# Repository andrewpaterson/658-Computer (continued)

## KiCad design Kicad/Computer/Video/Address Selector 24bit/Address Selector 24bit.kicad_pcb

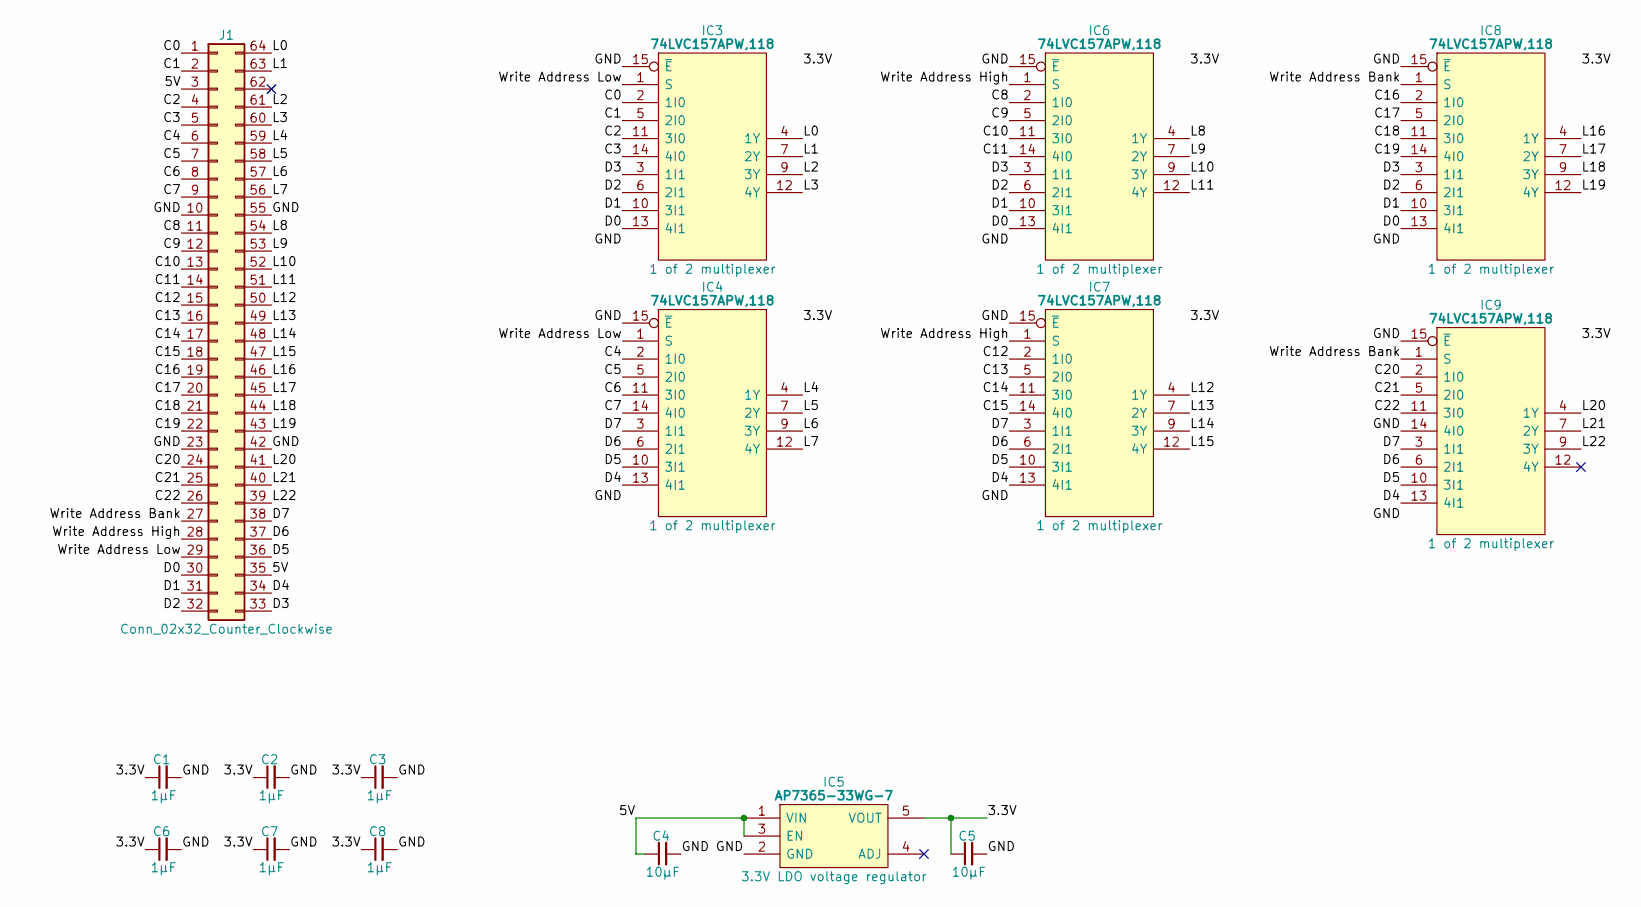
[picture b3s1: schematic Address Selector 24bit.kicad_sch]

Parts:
C1, C2, C3, C6, C7, C8: 1μF; C_0805
C4, C5: 10µF; C_0805
IC3, IC4, IC6, IC7, IC8, IC9: 74LVC157APW,118; SOP65P640X110-16N; Mouser Part Number 771-74LVC157APW-T
IC5: AP7365-33WG-7; SOT95P285X130-5N; Manufacturer_Part_Number AP7365-33WG-7; Mouser Part Number 621-AP7365-33WG-7
J1: Conn_02x32_Counter_Clockwise; DIP-64_Board_W15.24mm

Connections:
/3.3V: C1.1, C2.1, C3.1, C5.1, C6.1, C7.1, C8.1, IC3.16 (3V), IC4.16 (3V), IC5.5 (VOUT), IC6.16 (3V), IC7.16 (3V), IC8.16 (3V), IC9.16 (3V)
/5V: C4.1, IC5.1 (VIN), IC5.3 (EN), J1.3, J1.35
/C0: IC3.2 (1I0), J1.1
/C1: IC3.5 (2I0), J1.2
/C2: IC3.11 (3I0), J1.4
/C3: IC3.14 (4I0), J1.5
/C4: IC4.2 (1I0), J1.6
/C5: IC4.5 (2I0), J1.7
/C6: IC4.11 (3I0), J1.8
/C7: IC4.14 (4I0), J1.9
/C8: IC6.2 (1I0), J1.11
/C9: IC6.5 (2I0), J1.12
/C10: IC6.11 (3I0), J1.13
/C11: IC6.14 (4I0), J1.14
/C12: IC7.2 (1I0), J1.15
/C13: IC7.5 (2I0), J1.16
/C14: IC7.11 (3I0), J1.17
/C15: IC7.14 (4I0), J1.18
/C16: IC8.2 (1I0), J1.19
/C17: IC8.5 (2I0), J1.20
/C18: IC8.11 (3I0), J1.21
/C19: IC8.14 (4I0), J1.22
/C20: IC9.2 (1I0), J1.24
/C21: IC9.5 (2I0), J1.25
/C22: IC9.11 (3I0), J1.26
/D0: IC3.13 (4I1), IC6.13 (4I1), IC8.13 (4I1), J1.30
/D1: IC3.10 (3I1), IC6.10 (3I1), IC8.10 (3I1), J1.31
/D2: IC3.6 (2I1), IC6.6 (2I1), IC8.6 (2I1), J1.32
/D3: IC3.3 (1I1), IC6.3 (1I1), IC8.3 (1I1), J1.33
/D4: IC4.13 (4I1), IC7.13 (4I1), IC9.13 (4I1), J1.34
/D5: IC4.10 (3I1), IC7.10 (3I1), IC9.10 (3I1), J1.36
/D6: IC4.6 (2I1), IC7.6 (2I1), IC9.6 (2I1), J1.37
/D7: IC4.3 (1I1), IC7.3 (1I1), IC9.3 (1I1), J1.38
/GND: C1.2, C2.2, C3.2, C4.2, C5.2, C6.2, C7.2, C8.2, IC3.8 (GND), IC3.15 (~E), IC4.8 (GND), IC4.15 (~E), IC5.2 (GND), IC6.8 (GND), IC6.15 (~E), IC7.8 (GND), IC7.15 (~E), IC8.8 (GND), IC8.15 (~E), IC9.8 (GND), IC9.14 (4I0), IC9.15 (~E), J1.10, J1.23, J1.42, J1.55
/L0: IC3.4 (1Y), J1.64
/L1: IC3.7 (2Y), J1.63
/L2: IC3.9 (3Y), J1.61
/L3: IC3.12 (4Y), J1.60
/L4: IC4.4 (1Y), J1.59
/L5: IC4.7 (2Y), J1.58
/L6: IC4.9 (3Y), J1.57
/L7: IC4.12 (4Y), J1.56
/L8: IC6.4 (1Y), J1.54
/L9: IC6.7 (2Y), J1.53
/L10: IC6.9 (3Y), J1.52
/L11: IC6.12 (4Y), J1.51
/L12: IC7.4 (1Y), J1.50
/L13: IC7.7 (2Y), J1.49
/L14: IC7.9 (3Y), J1.48
/L15: IC7.12 (4Y), J1.47
/L16: IC8.4 (1Y), J1.46
/L17: IC8.7 (2Y), J1.45
/L18: IC8.9 (3Y), J1.44
/L19: IC8.12 (4Y), J1.43
/L20: IC9.4 (1Y), J1.41
/L21: IC9.7 (2Y), J1.40
/L22: IC9.9 (3Y), J1.39
/Write Address Bank: IC8.1 (S), IC9.1 (S), J1.27
/Write Address High: IC6.1 (S), IC7.1 (S), J1.28
/Write Address Low: IC3.1 (S), IC4.1 (S), J1.29

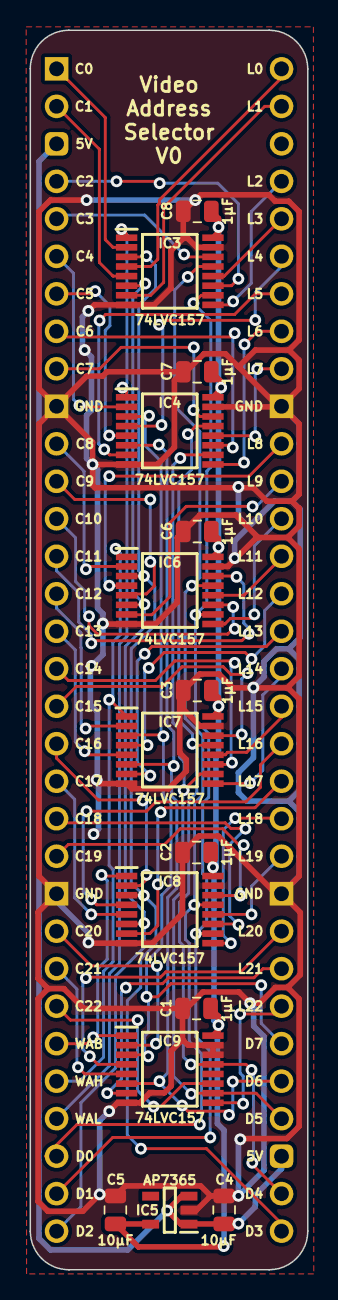
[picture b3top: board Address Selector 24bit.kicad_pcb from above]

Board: 2 copper layers, 18.8 x 84.0 mm, 16 parts (0 on the bottom side), 60 nets.

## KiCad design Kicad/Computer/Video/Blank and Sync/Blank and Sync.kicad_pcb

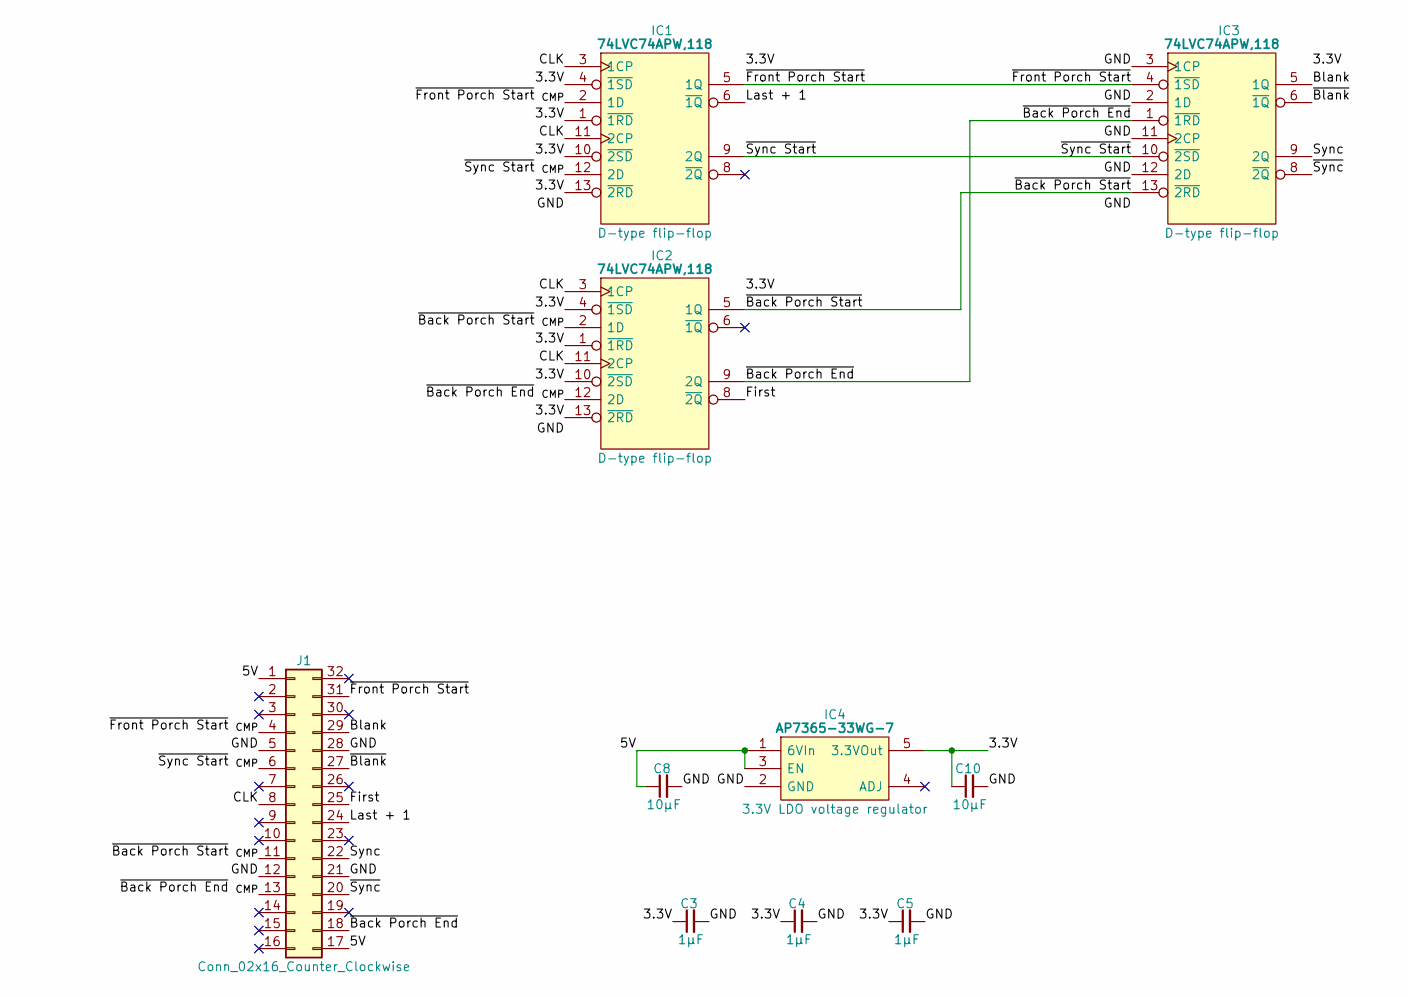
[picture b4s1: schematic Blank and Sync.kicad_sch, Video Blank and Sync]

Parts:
C3, C4, C5: 1μF; C_0805
C8, C10: 10µF; C_0805
IC1, IC2, IC3: 74LVC74APW,118; SOP65P640X110-14N; Mouser Part Number 771-74LVC74APW-T
IC4: AP7365-33WG-7; SOT95P285X130-5N; Manufacturer_Part_Number AP7365-33WG-7; Mouser Part Number 621-AP7365-33WG-7
J1: Conn_02x16_Counter_Clockwise; DIP-32_Board_W15.24mm

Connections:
/3.3V: C3.1, C4.1, C5.1, C10.1, IC1.1 (~1RD), IC1.4 (~1SD), IC1.10 (~2SD), IC1.13 (~2RD), IC1.14 (3V), IC2.1 (~1RD), IC2.4 (~1SD), IC2.10 (~2SD), IC2.13 (~2RD), IC2.14 (3V), IC3.14 (3V), IC4.5 (3.3VOut)
/5V: C8.1, IC4.1 (6VIn), IC4.3 (EN), J1.1, J1.17
/Blank: IC3.5 (1Q), J1.29
/CLK: IC1.3 (1CP), IC1.11 (2CP), IC2.3 (1CP), IC2.11 (2CP), J1.8
/First: IC2.8 (~2Q), J1.25
/GND: C3.2, C4.2, C5.2, C8.2, C10.2, IC1.7 (GND), IC2.7 (GND), IC3.2 (1D), IC3.3 (1CP), IC3.7 (GND), IC3.11 (2CP), IC3.12 (2D), IC4.2 (GND), J1.5, J1.12, J1.21, J1.28
/Last + 1: IC1.6 (~1Q), J1.24
/Sync: IC3.9 (2Q), J1.22
/~Back Porch End: IC2.9 (2Q), IC3.1 (~1RD), J1.18
/~Back Porch End _{CMP}: IC2.12 (2D), J1.13
/~Back Porch Start: IC2.5 (1Q), IC3.13 (~2RD)
/~Back Porch Start _{CMP}: IC2.2 (1D), J1.11
/~Blank: IC3.6 (~1Q), J1.27
/~Front Porch Start: IC1.5 (1Q), IC3.4 (~1SD), J1.31
/~Front Porch Start _{CMP}: IC1.2 (1D), J1.4
/~Sync Start: IC1.9 (2Q), IC3.10 (~2SD)
/~Sync Start _{CMP}: IC1.12 (2D), J1.6
/~Sync: IC3.8 (~2Q), J1.20

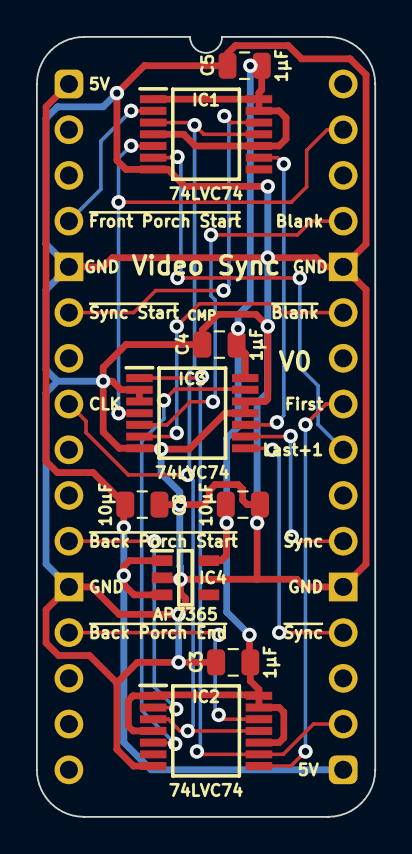
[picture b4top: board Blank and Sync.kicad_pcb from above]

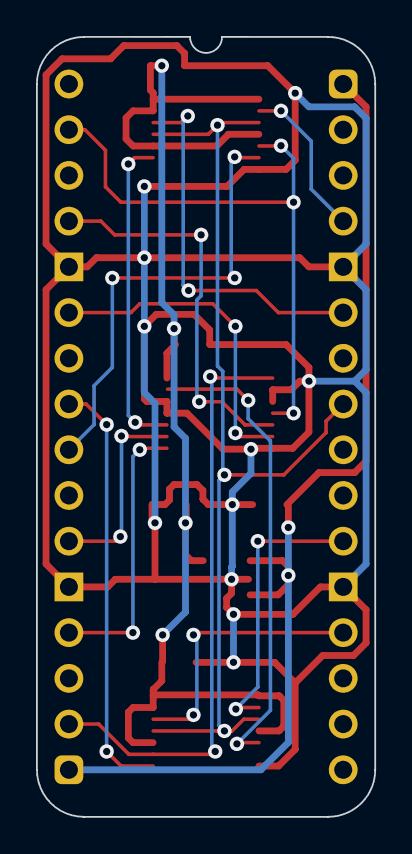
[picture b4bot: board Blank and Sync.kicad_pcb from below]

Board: 2 copper layers, 18.8 x 43.3 mm, 12 parts (2 on the bottom side), 18 nets.

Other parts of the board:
J2, J3: Pin_Header_01x16; PinHeader_1x16_P2.54mm_Vertical

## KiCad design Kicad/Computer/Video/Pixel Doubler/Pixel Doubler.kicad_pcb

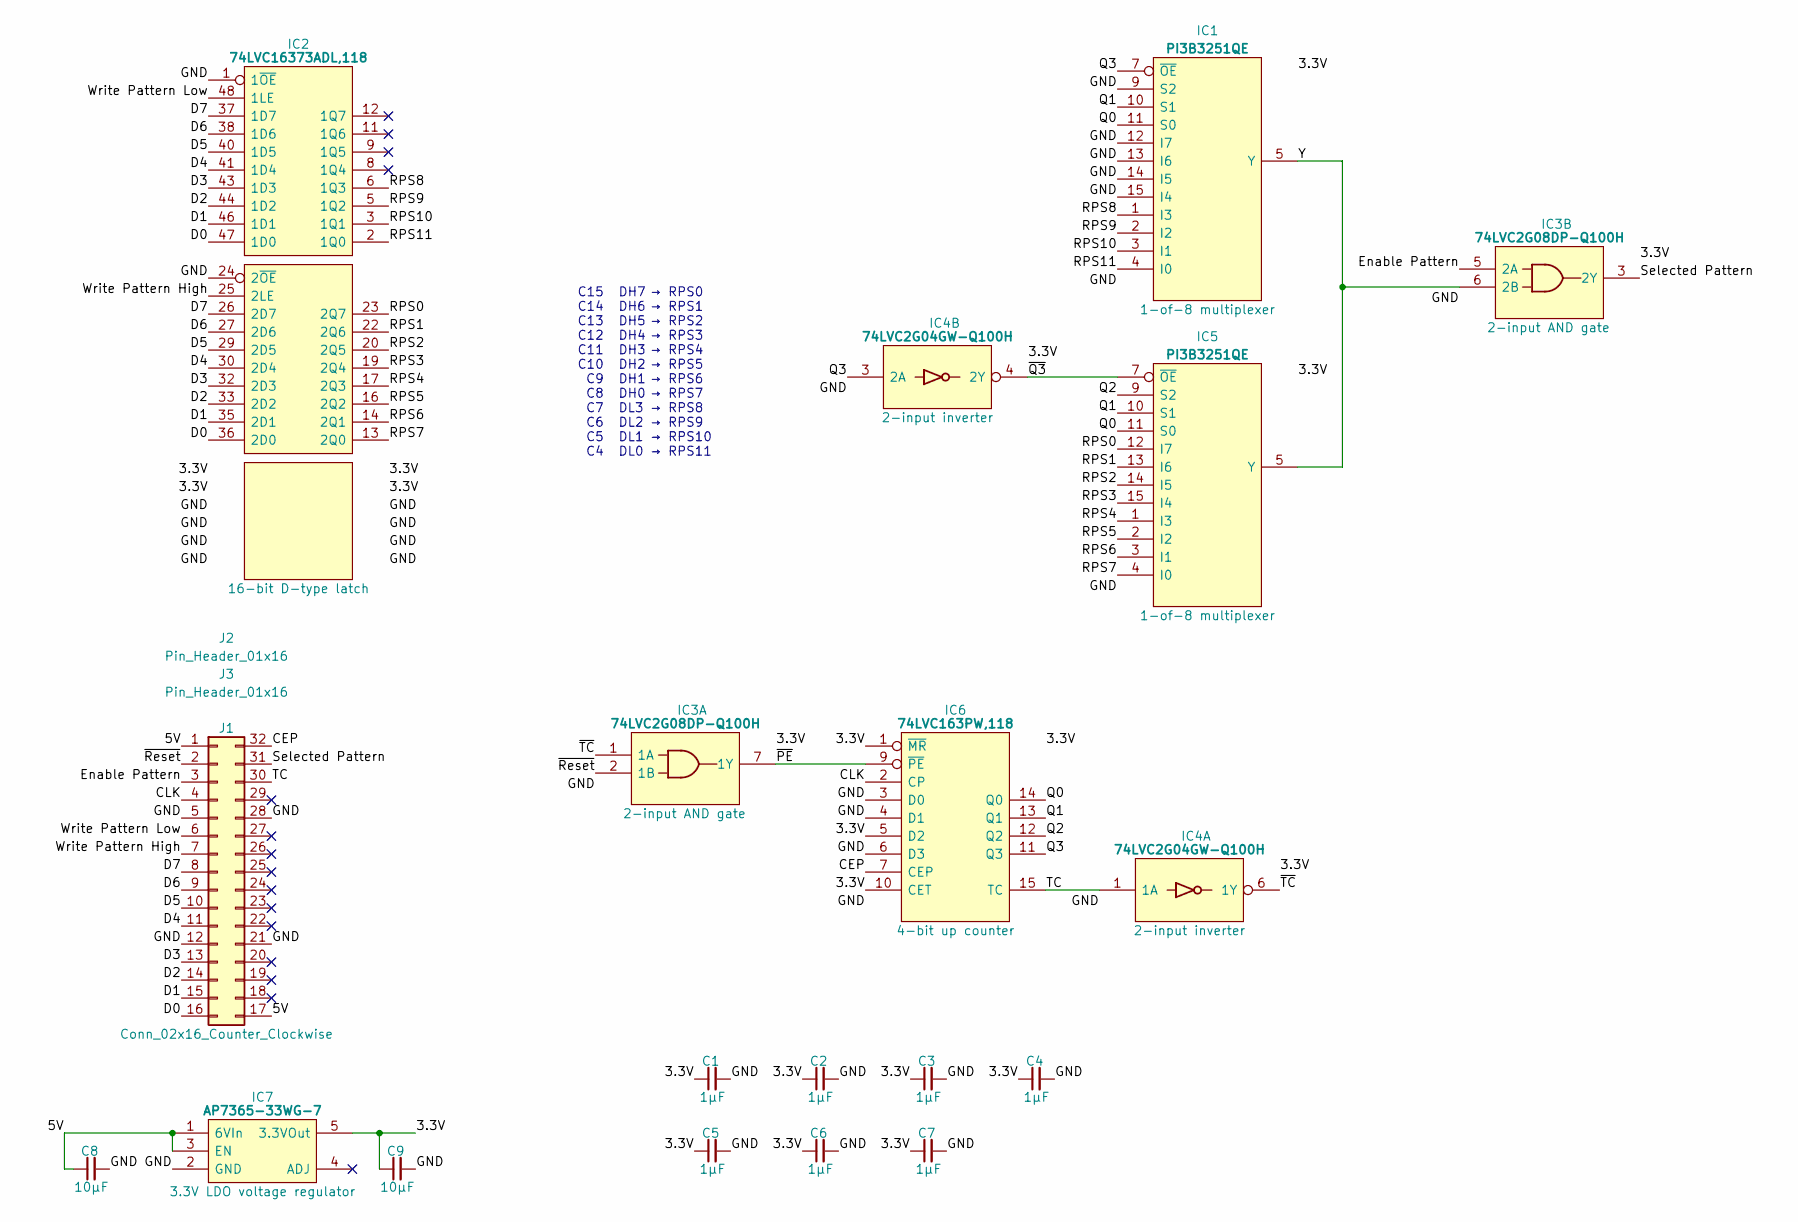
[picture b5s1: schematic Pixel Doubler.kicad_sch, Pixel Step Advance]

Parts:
C1, C2, C3, C4, C5, C6, C7: 1μF; C_0805
C8, C9: 10µF; C_0805
IC1, IC5: PI3B3251QE; SOP64P599X175-16N; Manufacturer_Part_Number PI3B3251QE; Mouser Part Number 729-PI3B3251QE
IC2: 74LVC16373ADL,118; SOP64P1025X280-48N; Mouser Part Number 771-LVC16373ADL118
IC3: 74LVC2G08DP-Q100H; SOP65P400X110-8N; Manufacturer_Part_Number 74LVC2G08DP-Q100H; Mouser Part Number 771-74LVC2G08DPQ100H
IC4: 74LVC2G04GW-Q100H; SOP65P210X110-6N; Manufacturer_Part_Number 74LVC2G04GW-Q100H; Mouser Part Number 771-74LVC2G04GWQ100H
IC6: 74LVC163PW,118; SOP65P640X110-16N; Mouser Part Number 771-74LVC163PW-T
IC7: AP7365-33WG-7; SOT95P285X130-5N; Manufacturer_Part_Number AP7365-33WG-7; Mouser Part Number 621-AP7365-33WG-7
J1: Conn_02x16_Counter_Clockwise; DIP-32_Board_W22.86mm
J2, J3: Pin_Header_01x16; PinHeader_1x16_P2.54mm_Vertical

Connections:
/3.3V: C1.1, C2.1, C3.1, C4.1, C5.1, C6.1, C7.1, C9.1, IC1.16 (3V), IC2.7 (3V), IC2.18 (3V), IC2.31 (3V), IC2.42 (3V), IC3.8 (3V), IC4.5 (3V), IC5.16 (3V), IC6.1 (~MR), IC6.5 (D2), IC6.10 (CET), IC6.16 (3V), IC7.5 (3.3VOut)
/5V: C8.1, IC7.1 (6VIn), IC7.3 (EN), J1.1, J1.17
/CEP: IC6.7 (CEP), J1.32
/CLK: IC6.2 (CP), J1.4
/D0: IC2.36 (2D0), IC2.47 (1D0), J1.16
/D1: IC2.35 (2D1), IC2.46 (1D1), J1.15
/D2: IC2.33 (2D2), IC2.44 (1D2), J1.14
/D3: IC2.32 (2D3), IC2.43 (1D3), J1.13
/D4: IC2.30 (2D4), IC2.41 (1D4), J1.11
/D5: IC2.29 (2D5), IC2.40 (1D5), J1.10
/D6: IC2.27 (2D6), IC2.38 (1D6), J1.9
/D7: IC2.26 (2D7), IC2.37 (1D7), J1.8
/Enable Pattern: IC3.5 (2A), J1.3
/GND: C1.2, C2.2, C3.2, C4.2, C5.2, C6.2, C7.2, C8.2, C9.2, IC1.8 (GND), IC1.9 (S2), IC1.12 (I7), IC1.13 (I6), IC1.14 (I5), IC1.15 (I4), IC2.1 (1~OE), IC2.4 (GND), IC2.10 (GND), IC2.15 (GND), IC2.21 (GND), IC2.24 (2~OE), IC2.28 (GND), IC2.34 (GND), IC2.39 (GND), IC2.45 (GND), IC3.4 (GND), IC4.2 (GND), IC5.8 (GND), IC6.3 (D0), IC6.4 (D1), IC6.6 (D3), IC6.8 (GND), IC7.2 (GND), J1.5, J1.12, J1.21, J1.28
/Q0: IC1.11 (S0), IC5.11 (S0), IC6.14 (Q0)
/Q1: IC1.10 (S1), IC5.10 (S1), IC6.13 (Q1)
/Q2: IC5.9 (S2), IC6.12 (Q2)
/Q3: IC1.7 (~OE), IC4.3 (2A), IC6.11 (Q3)
/RPS0: IC2.23 (2Q7), IC5.12 (I7)
/RPS1: IC2.22 (2Q6), IC5.13 (I6)
/RPS2: IC2.20 (2Q5), IC5.14 (I5)
/RPS3: IC2.19 (2Q4), IC5.15 (I4)
/RPS4: IC2.17 (2Q3), IC5.1 (I3)
/RPS5: IC2.16 (2Q2), IC5.2 (I2)
/RPS6: IC2.14 (2Q1), IC5.3 (I1)
/RPS7: IC2.13 (2Q0), IC5.4 (I0)
/RPS8: IC1.1 (I3), IC2.6 (1Q3)
/RPS9: IC1.2 (I2), IC2.5 (1Q2)
/RPS10: IC1.3 (I1), IC2.3 (1Q1)
/RPS11: IC1.4 (I0), IC2.2 (1Q0)
/Selected Pattern: IC3.3 (2Y), J1.31
/TC: IC4.1 (1A), IC6.15 (TC), J1.30
/Write Pattern High: IC2.25 (2LE), J1.7
/Write Pattern Low: IC2.48 (1LE), J1.6
/Y: IC1.5 (Y), IC3.6 (2B), IC5.5 (Y)
/~PE: IC3.7 (1Y), IC6.9 (~PE)
/~Q3: IC4.4 (2Y), IC5.7 (~OE)
/~Reset: IC3.2 (1B), J1.2
/~TC: IC3.1 (1A), IC4.6 (1Y)

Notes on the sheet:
C15 C14 C13 C12 C11 C10 C9 C8 C7 C6 C5 C4
DH7 DH6 DH5 DH4 DH3 DH2 DH1 DH0 DL3 DL2 DL1 DL0
→ RPS0 → RPS1 → RPS2 → RPS3 → RPS4 → RPS5 → RPS6 → RPS7 → RPS8 → RPS9 → RPS10 → RPS11

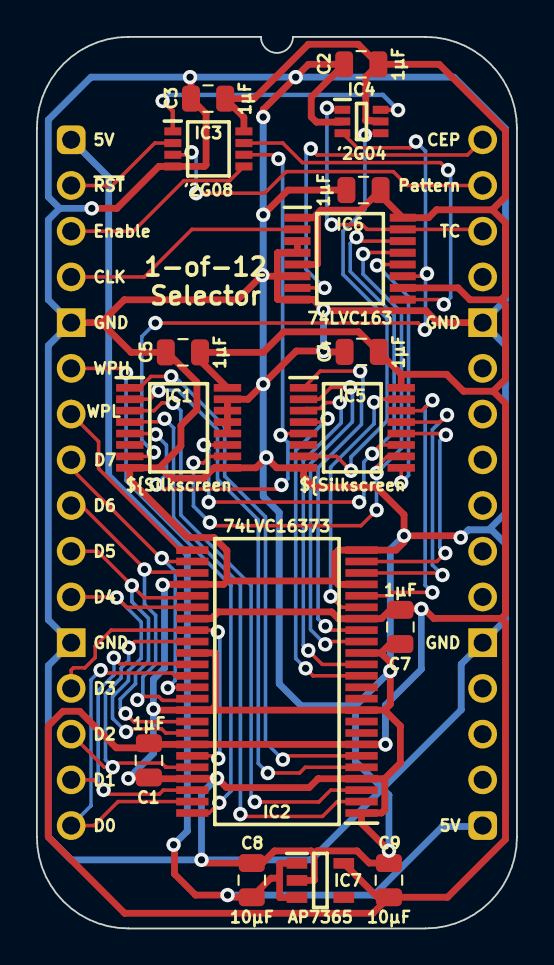
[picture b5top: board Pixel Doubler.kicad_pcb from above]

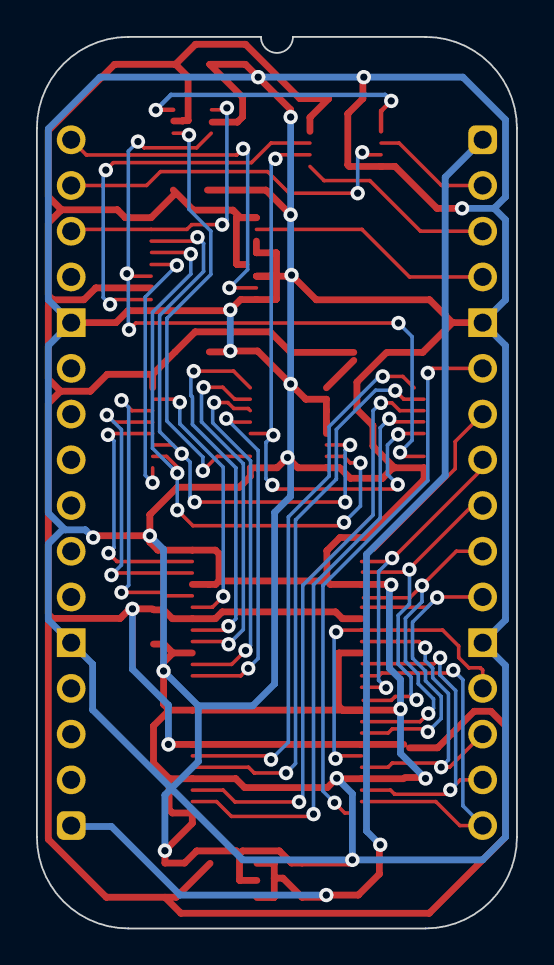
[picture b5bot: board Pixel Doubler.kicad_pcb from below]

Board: 2 copper layers, 26.7 x 49.5 mm, 19 parts (2 on the bottom side), 39 nets.

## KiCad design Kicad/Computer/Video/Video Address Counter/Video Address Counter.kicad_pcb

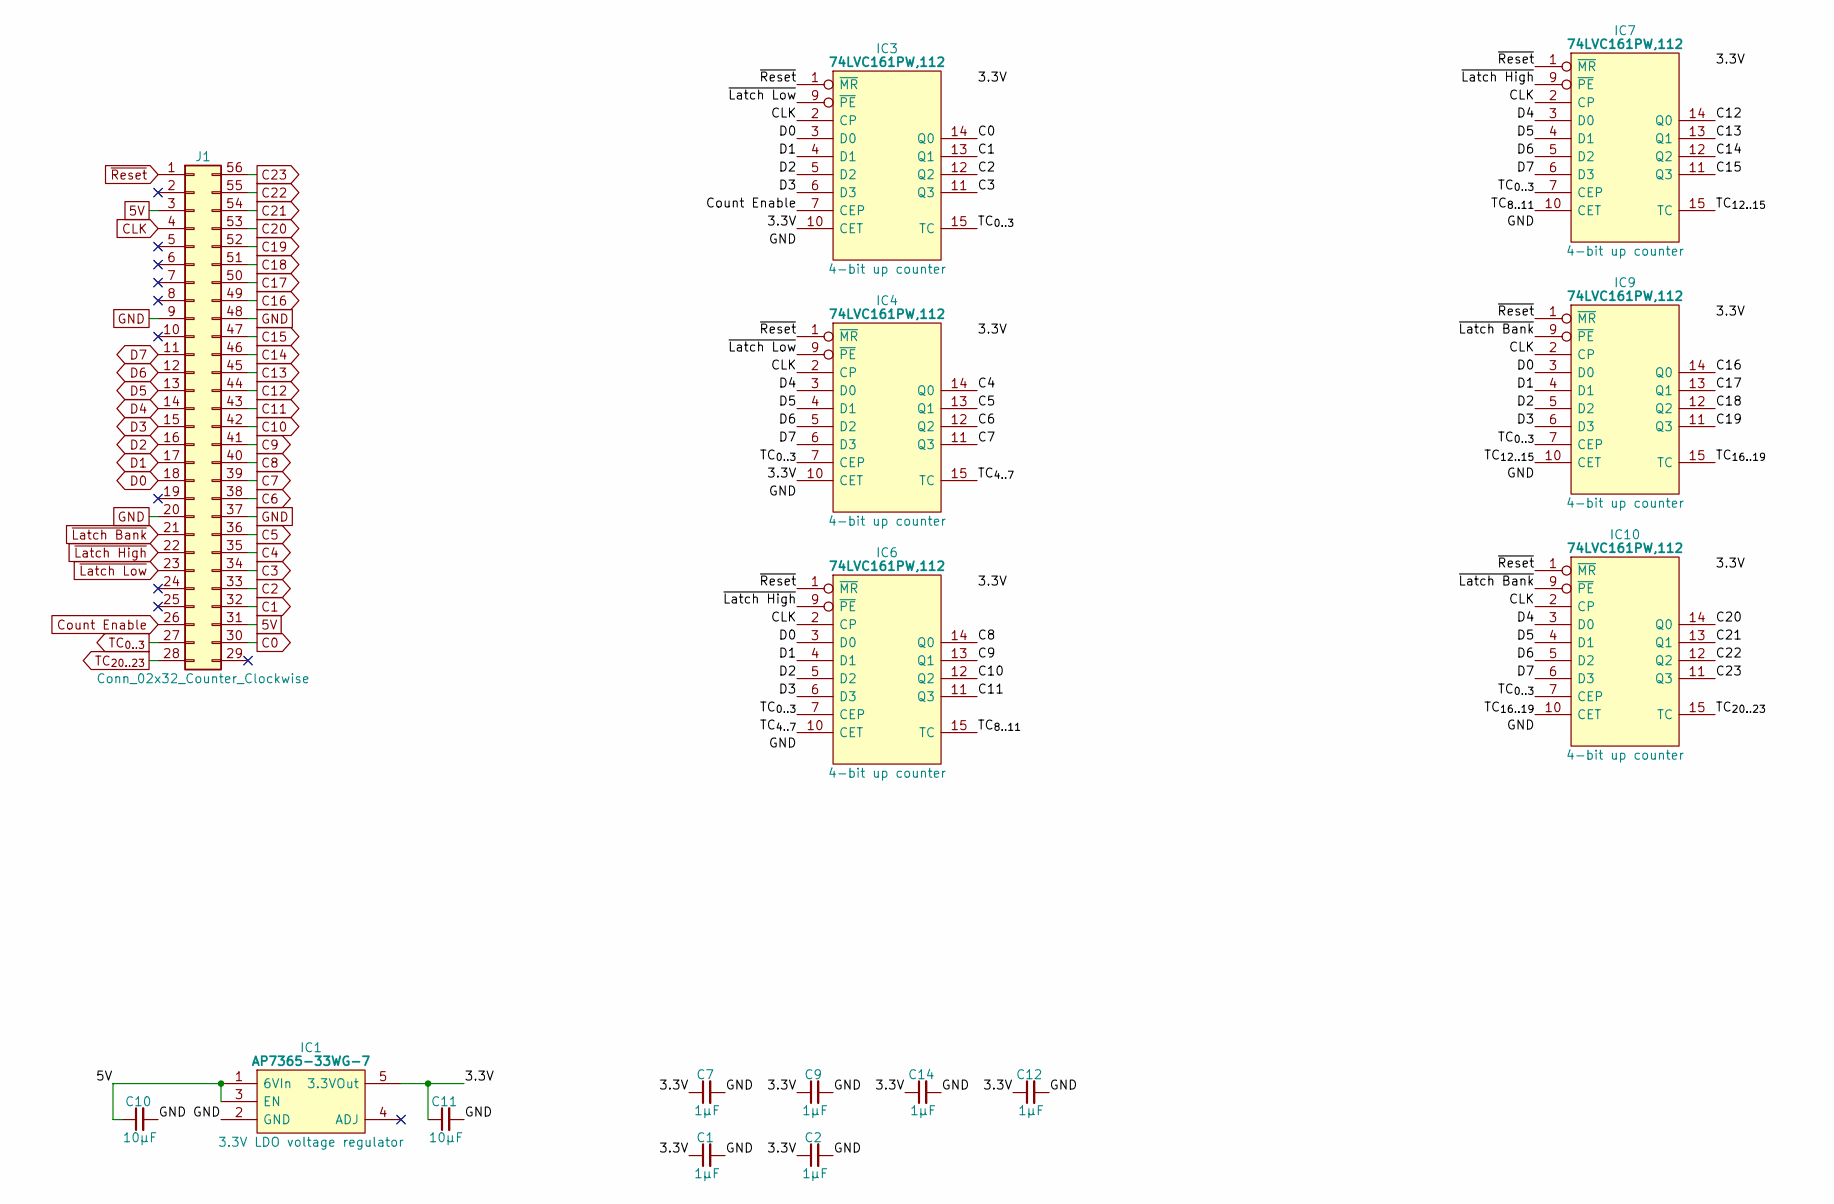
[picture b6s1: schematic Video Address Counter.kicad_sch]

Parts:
C1, C2, C7, C9, C12, C14: 1μF; C_0805
C10, C11: 10µF; C_0805
IC1: AP7365-33WG-7; SOT95P285X130-5N; Manufacturer_Part_Number AP7365-33WG-7; Mouser Part Number 621-AP7365-33WG-7
IC3, IC4, IC6, IC7, IC9, IC10: 74LVC161PW,112; SOP65P640X110-16N; Mouser Part Number 771-LVC161PW112
J1: Conn_02x32_Counter_Clockwise; DIP-56_Board_W15.24mm

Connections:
5V: C10.1, IC1.1 (6VIn), IC1.3 (EN), J1.3, J1.31
/3.3V: C1.1, C2.1, C7.1, C9.1, C11.1, C12.1, C14.1, IC1.5 (3.3VOut), IC3.10 (CET), IC3.16 (3V), IC4.10 (CET), IC4.16 (3V), IC6.16 (3V), IC7.16 (3V), IC9.16 (3V), IC10.16 (3V)
/TC_{4..7}: IC4.15 (TC), IC6.10 (CET)
/TC_{8..11}: IC6.15 (TC), IC7.10 (CET)
/TC_{12..15}: IC7.15 (TC), IC9.10 (CET)
/TC_{16..19}: IC9.15 (TC), IC10.10 (CET)
C0: IC3.14 (Q0), J1.30
C1: IC3.13 (Q1), J1.32
C2: IC3.12 (Q2), J1.33
C3: IC3.11 (Q3), J1.34
C4: IC4.14 (Q0), J1.35
C5: IC4.13 (Q1), J1.36
C6: IC4.12 (Q2), J1.38
C7: IC4.11 (Q3), J1.39
C8: IC6.14 (Q0), J1.40
C9: IC6.13 (Q1), J1.41
C10: IC6.12 (Q2), J1.42
C11: IC6.11 (Q3), J1.43
C12: IC7.14 (Q0), J1.44
C13: IC7.13 (Q1), J1.45
C14: IC7.12 (Q2), J1.46
C15: IC7.11 (Q3), J1.47
C16: IC9.14 (Q0), J1.49
C17: IC9.13 (Q1), J1.50
C18: IC9.12 (Q2), J1.51
C19: IC9.11 (Q3), J1.52
C20: IC10.14 (Q0), J1.53
C21: IC10.13 (Q1), J1.54
C22: IC10.12 (Q2), J1.55
C23: IC10.11 (Q3), J1.56
CLK: IC3.2 (CP), IC4.2 (CP), IC6.2 (CP), IC7.2 (CP), IC9.2 (CP), IC10.2 (CP), J1.4
Count Enable: IC3.7 (CEP), J1.26
D0: IC3.3 (D0), IC6.3 (D0), IC9.3 (D0), J1.18
D1: IC3.4 (D1), IC6.4 (D1), IC9.4 (D1), J1.17
D2: IC3.5 (D2), IC6.5 (D2), IC9.5 (D2), J1.16
D3: IC3.6 (D3), IC6.6 (D3), IC9.6 (D3), J1.15
D4: IC4.3 (D0), IC7.3 (D0), IC10.3 (D0), J1.14
D5: IC4.4 (D1), IC7.4 (D1), IC10.4 (D1), J1.13
D6: IC4.5 (D2), IC7.5 (D2), IC10.5 (D2), J1.12
D7: IC4.6 (D3), IC7.6 (D3), IC10.6 (D3), J1.11
GND: C1.2, C2.2, C7.2, C9.2, C10.2, C11.2, C12.2, C14.2, IC1.2 (GND), IC3.8 (GND), IC4.8 (GND), IC6.8 (GND), IC7.8 (GND), IC9.8 (GND), IC10.8 (GND), J1.9, J1.20, J1.37, J1.48
TC_{0..3}: IC3.15 (TC), IC4.7 (CEP), IC6.7 (CEP), IC7.7 (CEP), IC9.7 (CEP), IC10.7 (CEP), J1.27
TC_{20..23}: IC10.15 (TC), J1.28
~Latch Bank: IC9.9 (~PE), IC10.9 (~PE), J1.21
~Latch High: IC6.9 (~PE), IC7.9 (~PE), J1.22
~Latch Low: IC3.9 (~PE), IC4.9 (~PE), J1.23
~Reset: IC3.1 (~MR), IC4.1 (~MR), IC6.1 (~MR), IC7.1 (~MR), IC9.1 (~MR), IC10.1 (~MR), J1.1

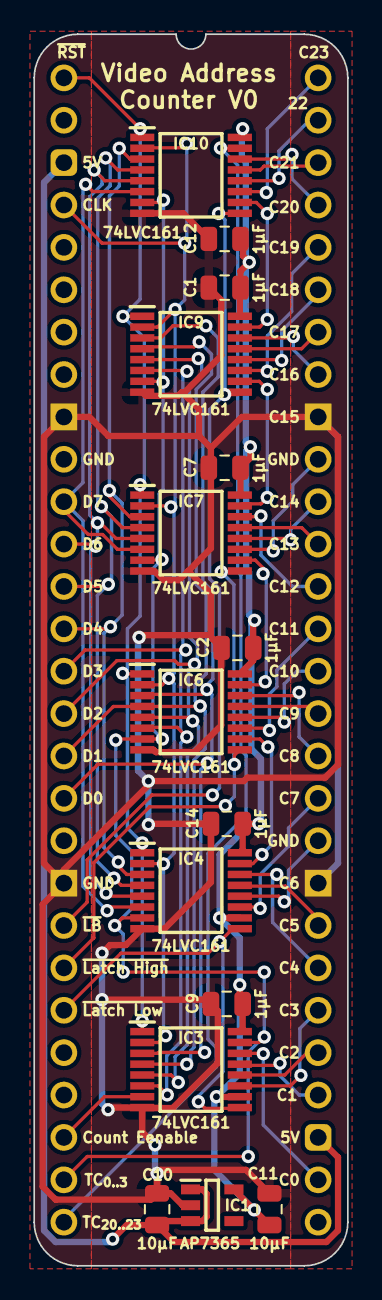
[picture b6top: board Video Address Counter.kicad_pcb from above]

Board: 2 copper layers, 18.8 x 73.8 mm, 16 parts (0 on the bottom side), 47 nets.

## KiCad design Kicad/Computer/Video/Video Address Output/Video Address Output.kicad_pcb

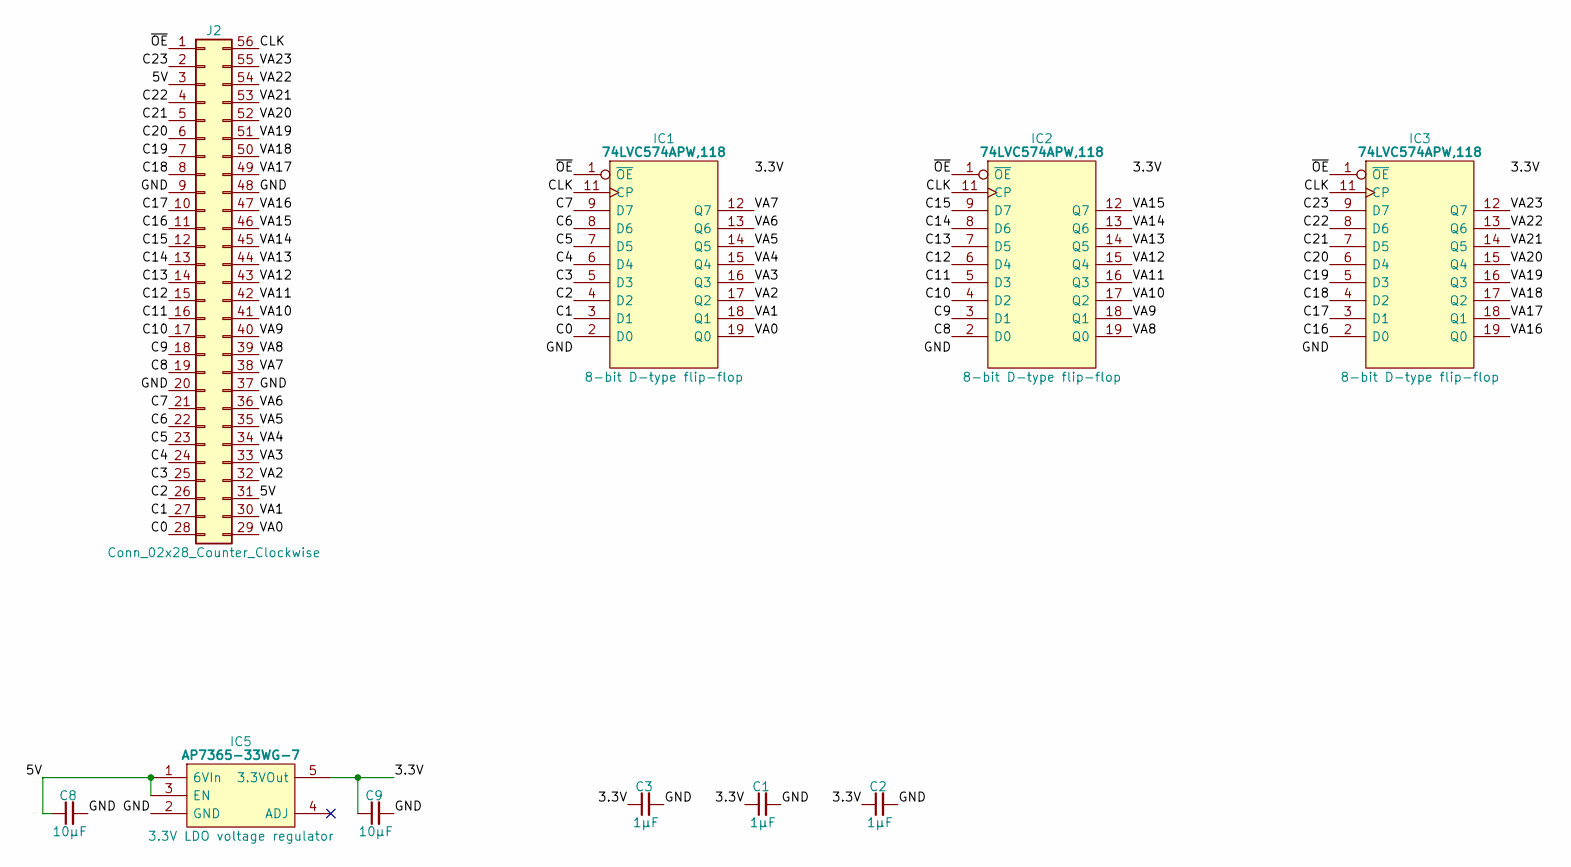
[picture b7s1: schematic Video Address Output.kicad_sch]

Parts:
C1, C2, C3: 1μF; C_0805
C8, C9: 10µF; C_0805
IC1, IC2, IC3: 74LVC574APW,118; SOP65P640X110-20N; Manufacturer_Part_Number 74LVC574APW,118; Mouser Part Number 771-74LVC574APW-T
IC5: AP7365-33WG-7; SOT95P285X130-5N; Manufacturer_Part_Number AP7365-33WG-7; Mouser Part Number 621-AP7365-33WG-7
J2: Conn_02x28_Counter_Clockwise; DIP-56_Board_W15.24mm

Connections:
/3.3V: C1.1, C2.1, C3.1, C9.1, IC1.20 (3V), IC2.20 (3V), IC3.20 (3V), IC5.5 (3.3VOut)
/5V: C8.1, IC5.1 (6VIn), IC5.3 (EN), J2.3, J2.31
/C0: IC1.2 (D0), J2.28
/C1: IC1.3 (D1), J2.27
/C2: IC1.4 (D2), J2.26
/C3: IC1.5 (D3), J2.25
/C4: IC1.6 (D4), J2.24
/C5: IC1.7 (D5), J2.23
/C6: IC1.8 (D6), J2.22
/C7: IC1.9 (D7), J2.21
/C8: IC2.2 (D0), J2.19
/C9: IC2.3 (D1), J2.18
/C10: IC2.4 (D2), J2.17
/C11: IC2.5 (D3), J2.16
/C12: IC2.6 (D4), J2.15
/C13: IC2.7 (D5), J2.14
/C14: IC2.8 (D6), J2.13
/C15: IC2.9 (D7), J2.12
/C16: IC3.2 (D0), J2.11
/C17: IC3.3 (D1), J2.10
/C18: IC3.4 (D2), J2.8
/C19: IC3.5 (D3), J2.7
/C20: IC3.6 (D4), J2.6
/C21: IC3.7 (D5), J2.5
/C22: IC3.8 (D6), J2.4
/C23: IC3.9 (D7), J2.2
/CLK: IC1.11 (CP), IC2.11 (CP), IC3.11 (CP), J2.56
/GND: C1.2, C2.2, C3.2, C8.2, C9.2, IC1.10 (GND), IC2.10 (GND), IC3.10 (GND), IC5.2 (GND), J2.9, J2.20, J2.37, J2.48
/VA0: IC1.19 (Q0), J2.29
/VA1: IC1.18 (Q1), J2.30
/VA2: IC1.17 (Q2), J2.32
/VA3: IC1.16 (Q3), J2.33
/VA4: IC1.15 (Q4), J2.34
/VA5: IC1.14 (Q5), J2.35
/VA6: IC1.13 (Q6), J2.36
/VA7: IC1.12 (Q7), J2.38
/VA8: IC2.19 (Q0), J2.39
/VA9: IC2.18 (Q1), J2.40
/VA10: IC2.17 (Q2), J2.41
/VA11: IC2.16 (Q3), J2.42
/VA12: IC2.15 (Q4), J2.43
/VA13: IC2.14 (Q5), J2.44
/VA14: IC2.13 (Q6), J2.45
/VA15: IC2.12 (Q7), J2.46
/VA16: IC3.19 (Q0), J2.47
/VA17: IC3.18 (Q1), J2.49
/VA18: IC3.17 (Q2), J2.50
/VA19: IC3.16 (Q3), J2.51
/VA20: IC3.15 (Q4), J2.52
/VA21: IC3.14 (Q5), J2.53
/VA22: IC3.13 (Q6), J2.54
/VA23: IC3.12 (Q7), J2.55
/~OE: IC1.1 (~OE), IC2.1 (~OE), IC3.1 (~OE), J2.1

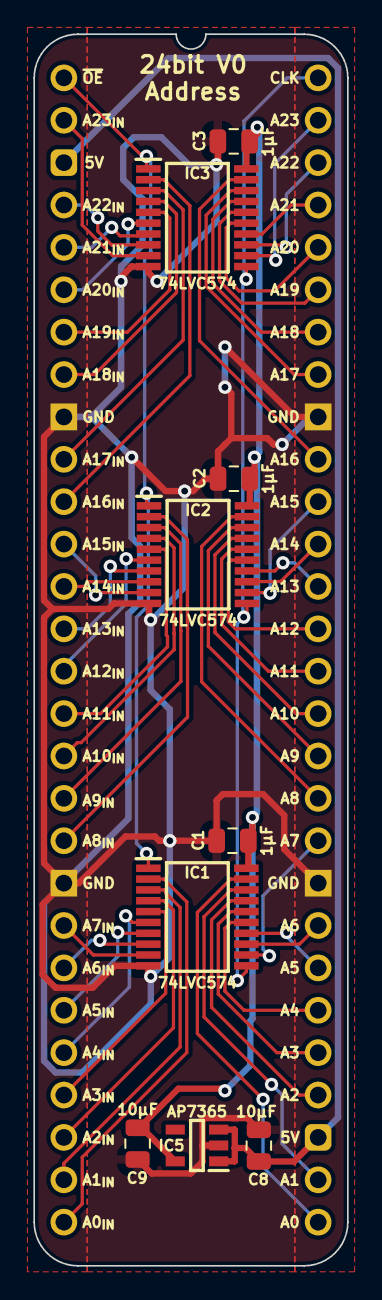
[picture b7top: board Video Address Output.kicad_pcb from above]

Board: 2 copper layers, 18.8 x 73.8 mm, 10 parts (0 on the bottom side), 53 nets.

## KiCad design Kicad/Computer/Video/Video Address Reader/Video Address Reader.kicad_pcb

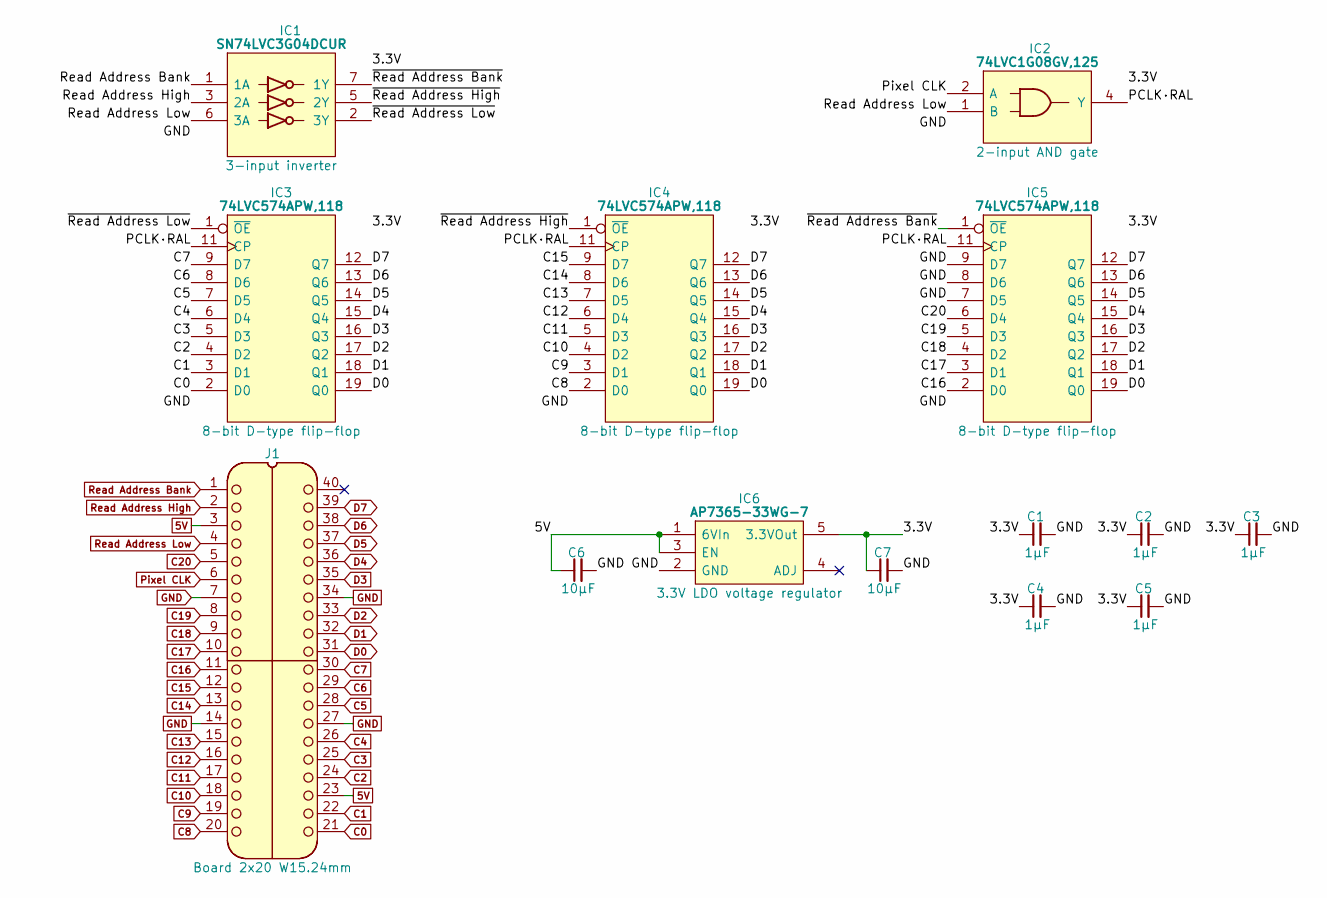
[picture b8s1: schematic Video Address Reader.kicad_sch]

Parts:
C1, C2, C3, C4, C5: 1μF; C_0805
C6, C7: 10µF; C_0805
IC1: SN74LVC3G04DCUR; SOP50P310X90-8N; Manufacturer_Part_Number SN74LVC3G04DCUR; Mouser Part Number 595-SN74LVC3G04DCUR
IC2: 74LVC1G08GV,125; SOT95P275X110-5N; Manufacturer_Part_Number 74LVC1G08GV,125; Mouser Part Number 771-74LVC1G08GV
IC3, IC4, IC5: 74LVC574APW,118; SOP65P640X110-20N; Manufacturer_Part_Number 74LVC574APW,118; Mouser Part Number 771-74LVC574APW-T
IC6: AP7365-33WG-7; SOT95P285X130-5N; Manufacturer_Part_Number AP7365-33WG-7; Mouser Part Number 621-AP7365-33WG-7
J1: Board 2x20 W15.24mm; DIP-40_Board_W15.24mm

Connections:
5V: C6.1, IC6.1 (6VIn), IC6.3 (EN), J1.3, J1.23
/3.3V: C1.1, C2.1, C3.1, C4.1, C5.1, C7.1, IC1.8 (3V), IC2.5 (3V), IC3.20 (3V), IC4.20 (3V), IC5.20 (3V), IC6.5 (3.3VOut)
/PCLK·RAL: IC2.4 (Y), IC3.11 (CP), IC4.11 (CP), IC5.11 (CP)
/~Read Address Bank: IC1.7 (1Y), IC5.1 (~OE)
/~Read Address High: IC1.5 (2Y), IC4.1 (~OE)
/~Read Address Low: IC1.2 (3Y), IC3.1 (~OE)
C0: IC3.2 (D0), J1.21
C1: IC3.3 (D1), J1.22
C2: IC3.4 (D2), J1.24
C3: IC3.5 (D3), J1.25
C4: IC3.6 (D4), J1.26
C5: IC3.7 (D5), J1.28
C6: IC3.8 (D6), J1.29
C7: IC3.9 (D7), J1.30
C8: IC4.2 (D0), J1.20
C9: IC4.3 (D1), J1.19
C10: IC4.4 (D2), J1.18
C11: IC4.5 (D3), J1.17
C12: IC4.6 (D4), J1.16
C13: IC4.7 (D5), J1.15
C14: IC4.8 (D6), J1.13
C15: IC4.9 (D7), J1.12
C16: IC5.2 (D0), J1.11
C17: IC5.3 (D1), J1.10
C18: IC5.4 (D2), J1.9
C19: IC5.5 (D3), J1.8
C20: IC5.6 (D4), J1.5
D0: IC3.19 (Q0), IC4.19 (Q0), IC5.19 (Q0), J1.31
D1: IC3.18 (Q1), IC4.18 (Q1), IC5.18 (Q1), J1.32
D2: IC3.17 (Q2), IC4.17 (Q2), IC5.17 (Q2), J1.33
D3: IC3.16 (Q3), IC4.16 (Q3), IC5.16 (Q3), J1.35
D4: IC3.15 (Q4), IC4.15 (Q4), IC5.15 (Q4), J1.36
D5: IC3.14 (Q5), IC4.14 (Q5), IC5.14 (Q5), J1.37
D6: IC3.13 (Q6), IC4.13 (Q6), IC5.13 (Q6), J1.38
D7: IC3.12 (Q7), IC4.12 (Q7), IC5.12 (Q7), J1.39
GND: C1.2, C2.2, C3.2, C4.2, C5.2, C6.2, C7.2, IC1.4 (GND), IC2.3 (GND), IC3.10 (GND), IC4.10 (GND), IC5.7 (D5), IC5.8 (D6), IC5.9 (D7), IC5.10 (GND), IC6.2 (GND), J1.7, J1.14, J1.27, J1.34
Pixel CLK: IC2.2 (A), J1.6
Read Address Bank: IC1.1 (1A), J1.1
Read Address High: IC1.3 (2A), J1.2
Read Address Low: IC1.6 (3A), IC2.1 (B), J1.4

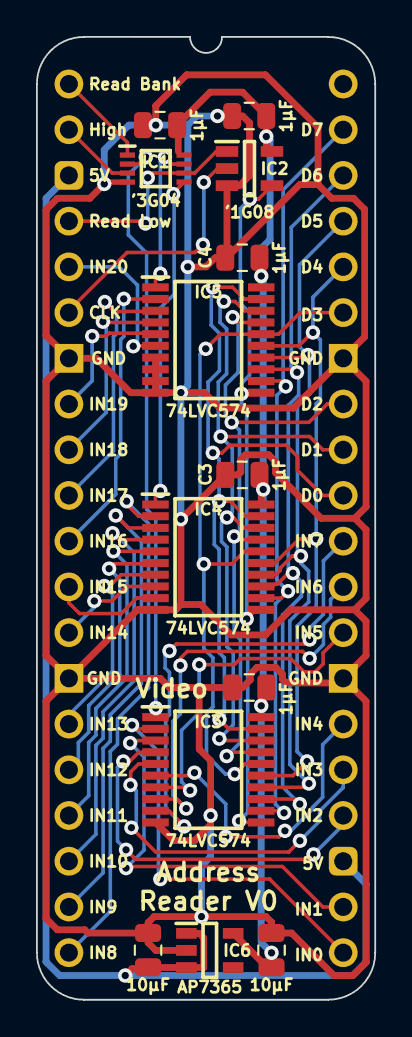
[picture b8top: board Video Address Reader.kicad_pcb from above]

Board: 2 copper layers, 18.8 x 53.5 mm, 14 parts (0 on the bottom side), 40 nets.
